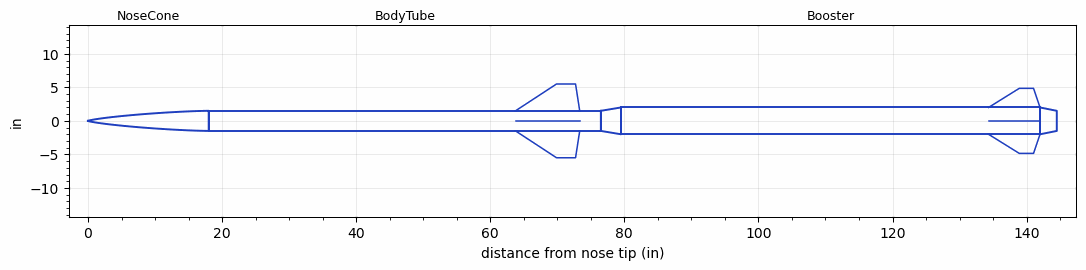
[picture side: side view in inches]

<RASAeroDocument>
 <FileVersion>2</FileVersion>
 <RocketDesign>
  <NoseCone>
   <Length>18</Length>
   <Diameter>3</Diameter>
   <Shape>Von Karman Ogive</Shape>
   <Location>0</Location>
  </NoseCone>
  <BodyTube>
   <Length>58.5</Length>
   <Diameter>3</Diameter>
   <Location>18</Location>
   <Fin>
    <Count>4</Count>
    <Chord>9.57</Chord>
    <Span>4</Span>
    <SweepDistance>6.11</SweepDistance>
    <TipChord>2.84</TipChord>
    <Thickness>0.125</Thickness>
    <LERadius>0.08</LERadius>
    <Location>12.73</Location>
    <AirfoilSection>Hexagonal</AirfoilSection>
    <FX1>0.5</FX1>
    <FX3>0.5</FX3>
   </Fin>
  </BodyTube>
  <Booster>
   <Length>62.5</Length>
   <Diameter>4</Diameter>
   <InsideDiameter>3</InsideDiameter>
   <Location>76.5</Location>
   <ShoulderLength>3</ShoulderLength>
   <BoattailLength>2.5</BoattailLength>
   <BoattailRearDiameter>3</BoattailRearDiameter>
   <Fin>
    <Count>4</Count>
    <Chord>7.675</Chord>
    <Span>2.85</Span>
    <SweepDistance>4.58</SweepDistance>
    <TipChord>2.13</TipChord>
    <Thickness>0.125</Thickness>
    <LERadius>0.08</LERadius>
    <Location>7.675</Location>
    <AirfoilSection>Hexagonal</AirfoilSection>
    <FX1>0.5</FX1>
    <FX3>0.5</FX3>
   </Fin>
  </Booster>
  <Surface>Rough Camouflage Paint</Surface>
  <ModifiedBarrowman>True</ModifiedBarrowman>
  <Turbulence>True</Turbulence>
  <UseBooster1>False</UseBooster1>
  <UseBooster2>False</UseBooster2>
 </RocketDesign>
 <LaunchSite>
  <Altitude>3000</Altitude>
  <Pressure>0</Pressure>
  <RodAngle>2</RodAngle>
  <RodLength>18</RodLength>
  <Temperature>85</Temperature>
  <WindSpeed>8</WindSpeed>
 </LaunchSite>
 <Recovery>
  <Altitude1>1000</Altitude1>
  <Altitude2>1000</Altitude2>
  <DeviceType1>None</DeviceType1>
  <DeviceType2>None</DeviceType2>
  <Event1>False</Event1>
  <Event2>False</Event2>
  <Size1>1</Size1>
  <Size2>1</Size2>
  <EventType1>None</EventType1>
  <EventType2>None</EventType2>
  <CD1>1.33</CD1>
  <CD2>1.33</CD2>
 </Recovery>
 <SimulationList>
  <Simulation>
   <SustainerEngine>M-1852  (M-1852)</SustainerEngine>
   <SustainerLaunchWt>24.7</SustainerLaunchWt>
   <SustainerNozzleDiameter>2.8</SustainerNozzleDiameter>
   <SustainerCG>41.8</SustainerCG>
   <SustainerIgnitionDelay>5</SustainerIgnitionDelay>
   <Booster1Engine>N-2857  (N-2857)</Booster1Engine>
   <Booster1LaunchWt>65.3</Booster1LaunchWt>
   <Booster1SeparationDelay>5</Booster1SeparationDelay>
   <Booster1IgnitionDelay>0</Booster1IgnitionDelay>
   <Booster1CG>75.58</Booster1CG>
   <Booster1NozzleDiameter>2.65</Booster1NozzleDiameter>
   <IncludeBooster1>True</IncludeBooster1>
   <Booster2Delay>0</Booster2Delay>
   <IncludeBooster2>False</IncludeBooster2>
   <TimetoApogee>64.70683</TimetoApogee>
   <MaxAltitude>60331.18</MaxAltitude>
   <MaxVelocity>2721.744</MaxVelocity>
  </Simulation>
 </SimulationList>
</RASAeroDocument>
